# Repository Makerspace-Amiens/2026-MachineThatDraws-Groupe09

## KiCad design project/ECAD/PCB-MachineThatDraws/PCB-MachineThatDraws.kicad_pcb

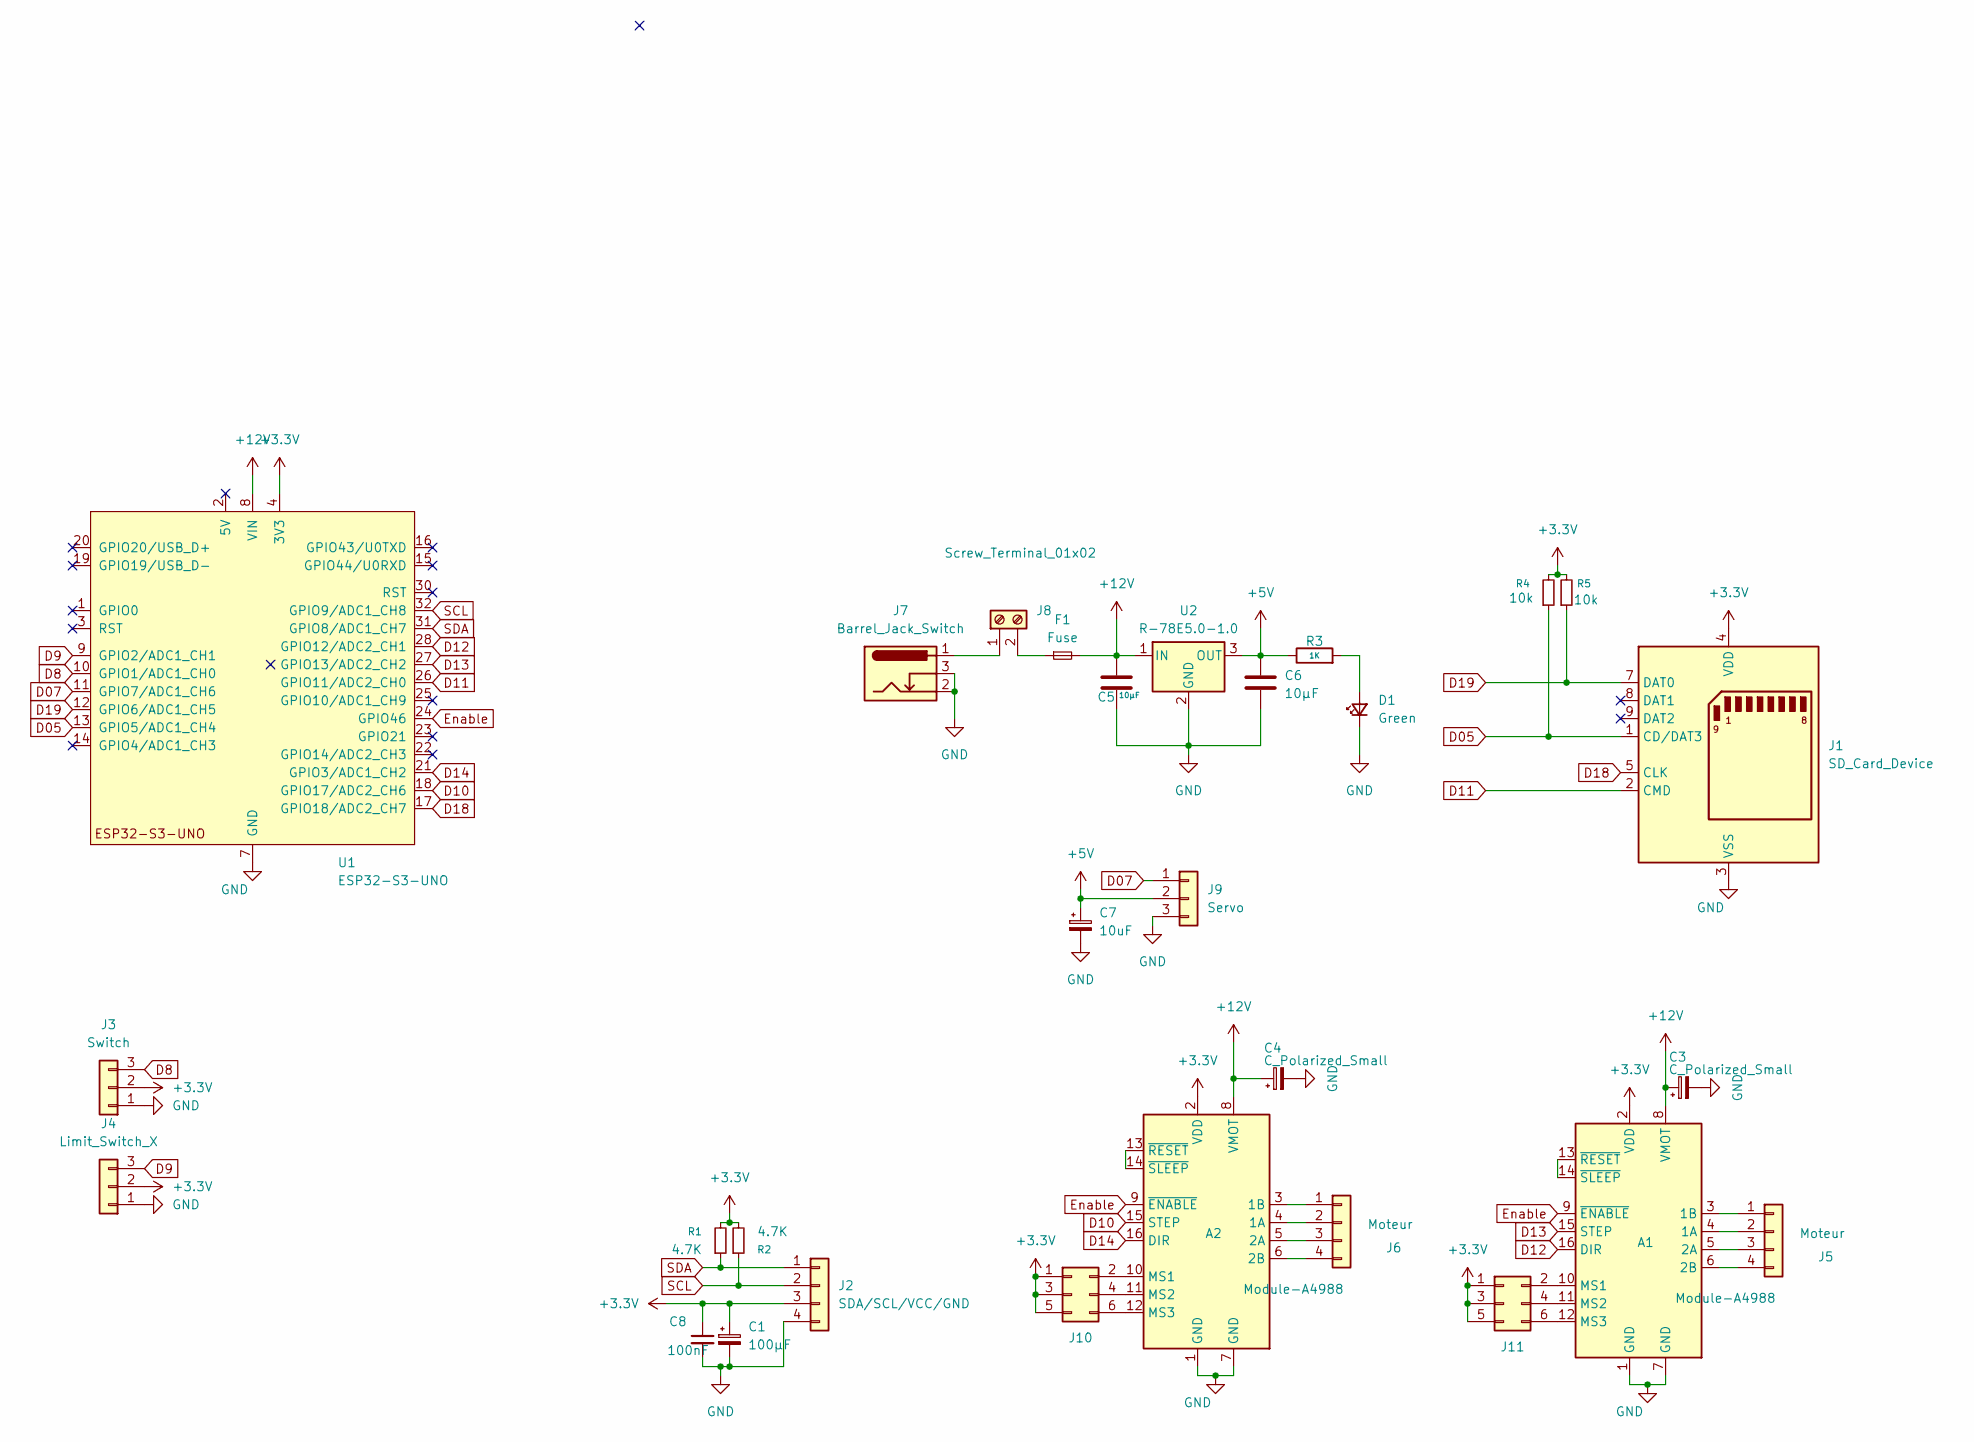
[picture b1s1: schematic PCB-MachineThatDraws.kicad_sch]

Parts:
A1, A2: Module-A4988; Pololu_Breakout-16_15.2x20.3mm
C1: 100µF; C_1206
C3, C4: C_Polarized_Small; CP_Elec_6.3x5.4
C5, C6: 10µF; C_1206
C7: 10uF; C_1206
C8: 100nF; C_1206
D1: Green; LED_1206_3216Metric
F1: Fuse; Fuseholder_Blade_Mini_Keystone_3568
J1: SD_Card_Device; SD_Hirose_DM1AA_SF_PEJ82
J2: SDA/SCL/VCC/GND; NS-Tech_Grove_1x04_P2mm_Vertical
J3: Switch; PinHeader_1x03_P2.54mm_Vertical
J4: Limit_Switch_X; PinHeader_1x03_P2.54mm_Vertical
J5, J6: Moteur; PinHeader_1x04_P2.54mm_Vertical
J7: Barrel_Jack_Switch; BarrelJack_GCT_DCJ200-10-A_Horizontal
J8: Screw_Terminal_01x02; TerminalBlock_bornier-2_P5.08mm
J9: Servo; PinHeader_1x03_P2.54mm_Vertical
J10, J11: Conn_02x03_Odd_Even; PinHeader_2x03_P2.54mm_Vertical
R1, R2: 4.7K; R_1206
R3: 1K; R_1206
R4, R5: 10k; R_1206
U1: ESP32-S3-UNO; ESP_S3_UNO
U2: R-78E5.0-1.0; Converter_DCDC_RECOM_R-78E-0.5_THT

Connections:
+3.3V: A1.2 (VDD), A2.2 (VDD), C1.1, C8.1, J1.4 (VDD), J2.3, J3.2, J4.2, J10.1, J10.3, J10.5, J11.1, J11.3, J11.5, R1.2, R2.2, R4.2, R5.2, U1.4 (3V3)
+5V: C6.1, C7.1, J9.2, R3.1, U2.3 (OUT)
+12V: A1.8 (VMOT), A2.8 (VMOT), C3.1, C4.1, C5.1, F1.2, U1.8 (VIN), U2.1 (IN)
D05: J1.1 (CD/DAT3), R4.1, U1.13 (GPIO5/ADC1_CH4)
D07: J9.1, U1.11 (GPIO7/ADC1_CH6)
D8: J3.3, U1.10 (GPIO1/ADC1_CH0)
D9: J4.3, U1.9 (GPIO2/ADC1_CH1)
D10: A2.15 (STEP), U1.18 (GPIO17/ADC2_CH6)
D11: J1.2 (CMD), U1.26 (GPIO11/ADC2_CH0)
D12: A1.16 (DIR), U1.28 (GPIO12/ADC2_CH1)
D13: A1.15 (STEP), U1.27 (GPIO13/ADC2_CH2)
D14: A2.16 (DIR), U1.21 (GPIO3/ADC1_CH2)
D18: J1.5 (CLK), U1.17 (GPIO18/ADC2_CH7)
D19: J1.7 (DAT0), R5.1, U1.12 (GPIO6/ADC1_CH5)
Enable: A1.9 (~ENABLE), A2.9 (~ENABLE), U1.24 (GPIO46)
GND: A1.1 (GND), A1.7 (GND), A2.1 (GND), A2.7 (GND), C1.2, C3.2, C4.2, C5.2, C6.2, C7.2, C8.2, D1.1 (K), J1.3 (VSS), J1.6 (VSS), J2.4, J3.1, J4.1, J7.2, J7.3, J9.3, U1.6 (GND), U1.7 (GND), U1.29 (GND), U2.2 (GND)
unnamed: A1.4 (1A), J5.2
unnamed: A1.3 (1B), J5.1
unnamed: A1.5 (2A), J5.3
unnamed: A1.6 (2B), J5.4
unnamed: A1.10 (MS1), J11.2
unnamed: A1.11 (MS2), J11.4
unnamed: A1.12 (MS3), J11.6
unnamed: A1.13 (~RESET), A1.14 (~SLEEP)
unnamed: A2.4 (1A), J6.2
unnamed: A2.3 (1B), J6.1
unnamed: A2.5 (2A), J6.3
unnamed: A2.6 (2B), J6.4
unnamed: A2.10 (MS1), J10.2
unnamed: A2.11 (MS2), J10.4
unnamed: A2.12 (MS3), J10.6
unnamed: A2.13 (~RESET), A2.14 (~SLEEP)
unnamed: D1.2 (A), R3.2
unnamed: J7.1, J8.1
unnamed: F1.1, J8.2
SCL: U1.32 (GPIO9/ADC1_CH8)
SCL: J2.2, R2.1
SDA: J2.1, R1.1
SDA: U1.31 (GPIO8/ADC1_CH7)

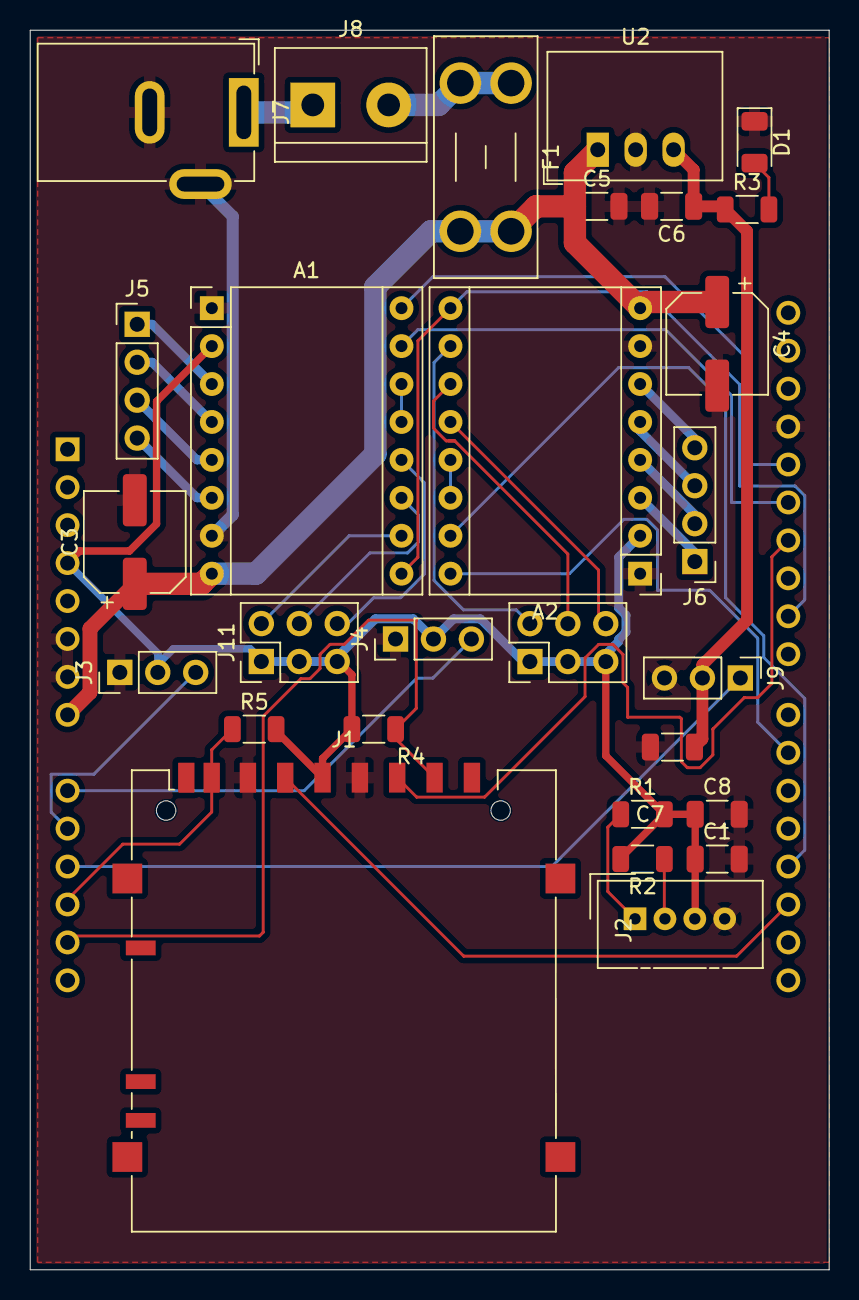
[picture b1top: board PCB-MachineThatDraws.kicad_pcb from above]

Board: 2 copper layers, 53.5 x 83.0 mm, 29 parts (0 on the bottom side), 37 nets.

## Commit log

2026-04-27 Rename PCB-MachineThatDraws v2.kicad_pcb to PCB-MachineThatDraws.kicad_pcb
2026-04-27 pcb up
2026-05-06 pcb + sch up
2026-05-06 pcb opti
2026-05-06 pcb up, 0 erreurs au drc
2026-05-11 pcb correction
2026-05-12 essai
2026-05-12 modif
2026-05-12 style
2026-05-19 ifjlhsq
2026-05-19 updtae
2026-05-22 Revert "update"
    This reverts commit ec935e6b940c2c5bda8e91ddcf084f28077f5bfb.
2026-05-22 test vidéo
2026-05-22 test video
2026-06-01 piece
2026-06-04 truc de chose
2026-06-05 etudes
2026-06-06 last update peut etre
